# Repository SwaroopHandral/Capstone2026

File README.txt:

wsg chat
first commit type shit

new

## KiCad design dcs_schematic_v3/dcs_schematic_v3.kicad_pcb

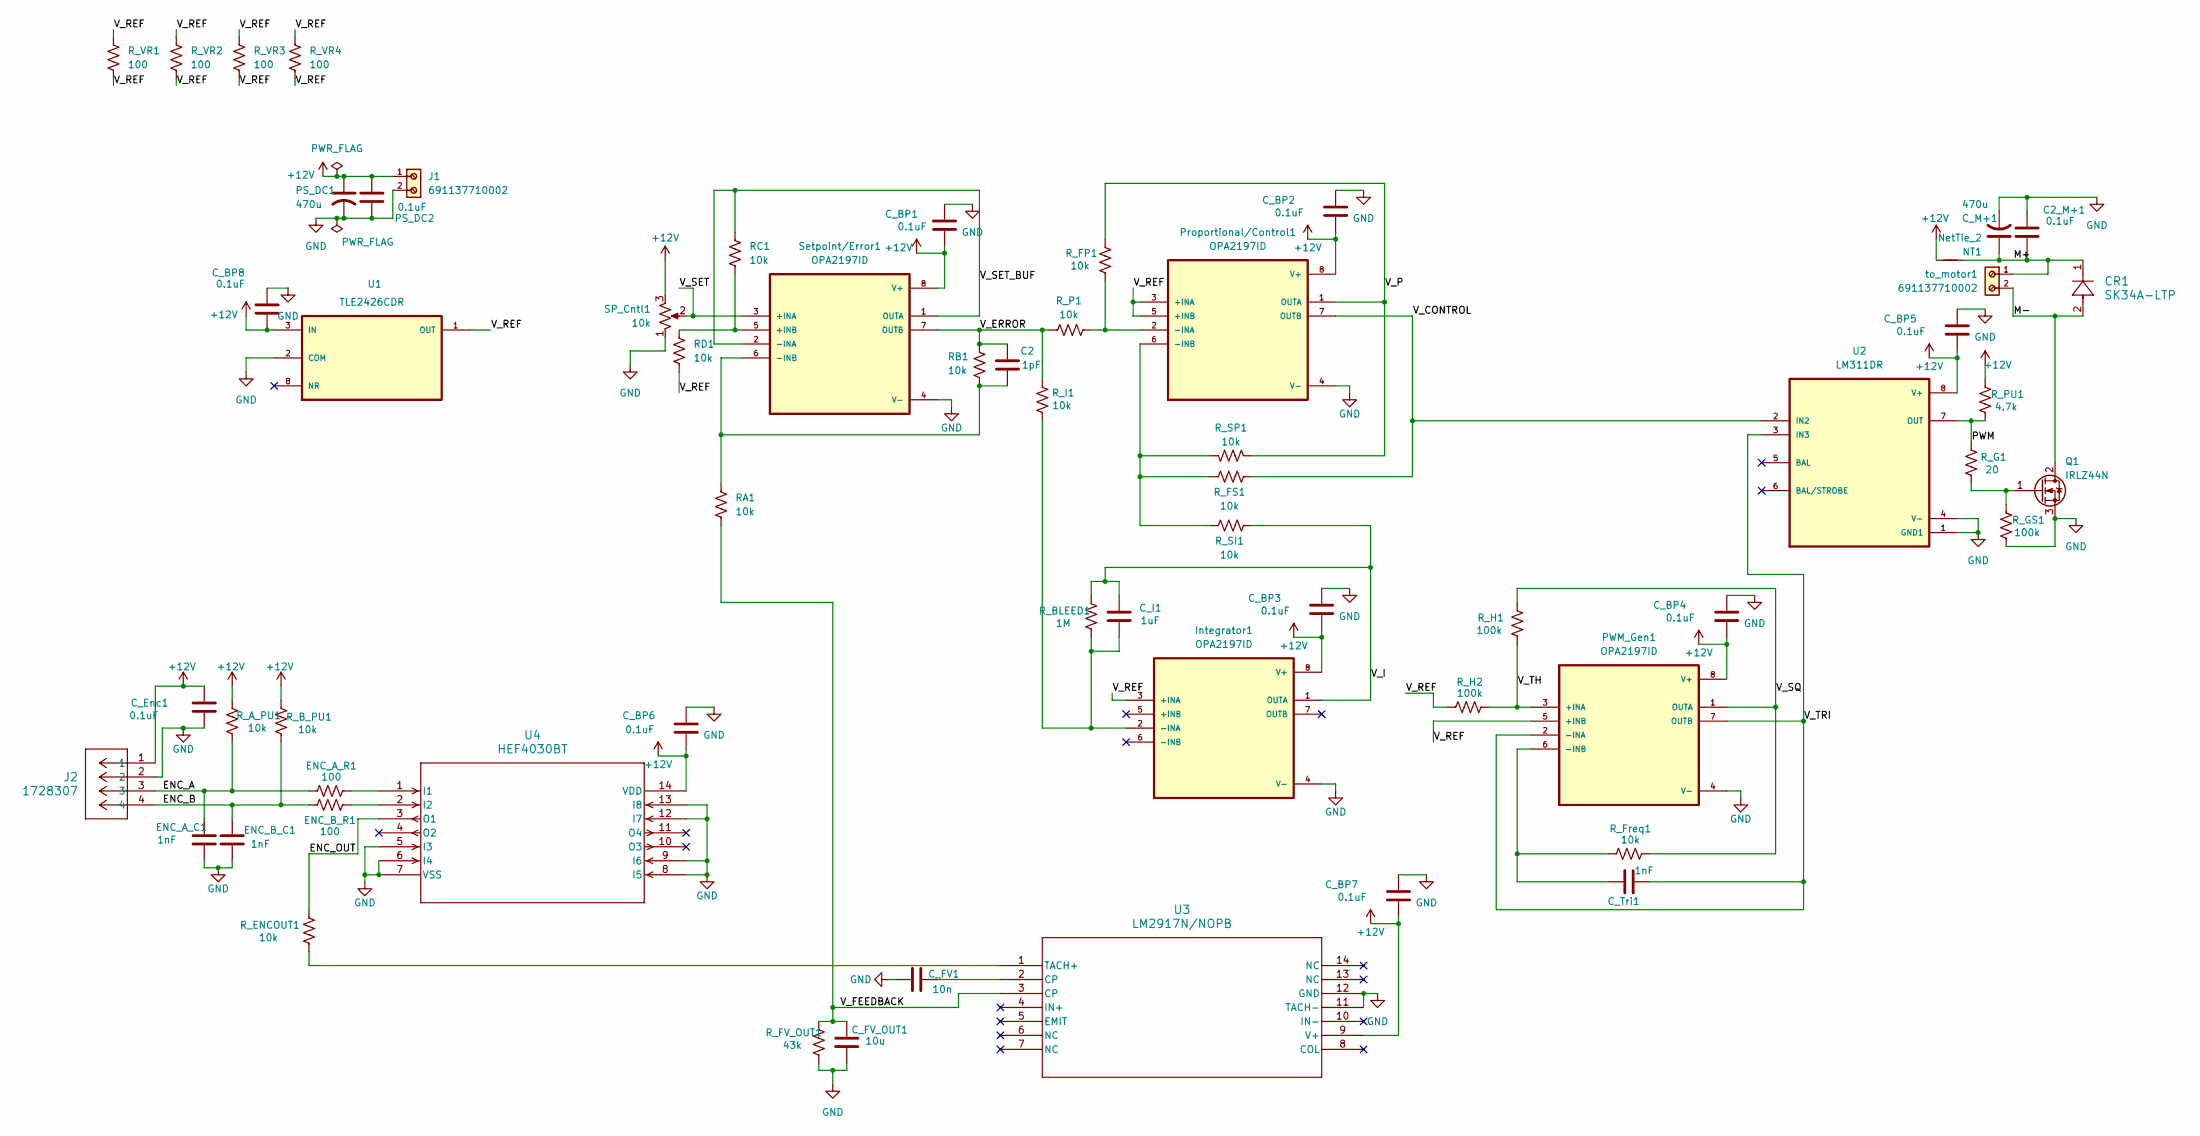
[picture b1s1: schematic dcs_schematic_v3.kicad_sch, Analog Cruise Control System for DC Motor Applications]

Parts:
C2: 1pF; C_0603_1608Metric_Pad1.08x0.95mm_HandSolder
C2_M+1: 0.1uF; C_0603_1608Metric_Pad1.08x0.95mm_HandSolder
CR1: SK34A-LTP; SK32A-LTP_Diode
C_BP1, C_BP2, C_BP3, C_BP4, C_BP5, C_BP6, C_BP7, C_BP8: 0.1uF; C_0603_1608Metric_Pad1.08x0.95mm_HandSolder
C_Enc1: 0.1uF; C_0603_1608Metric_Pad1.08x0.95mm_HandSolder
C_FV1: 10n; C_0603_1608Metric_Pad1.08x0.95mm_HandSolder
C_FV_OUT1: 10u; C_0603_1608Metric_Pad1.08x0.95mm_HandSolder
C_I1: 1uF; C_0603_1608Metric_Pad1.08x0.95mm_HandSolder
C_M+1: 470u; CP_Radial_D10.0mm_P5.00mm
C_Tri1: 1nF; C_0603_1608Metric_Pad1.08x0.95mm_HandSolder
ENC_A_C1: 1nF; C_0603_1608Metric_Pad1.08x0.95mm_HandSolder
ENC_A_R1: 100; R_0603_1608Metric_Pad0.98x0.95mm_HandSolder
ENC_B_C1: 1nF; C_0603_1608Metric_Pad1.08x0.95mm_HandSolder
ENC_B_R1: 100; R_0603_1608Metric_Pad0.98x0.95mm_HandSolder
Integrator1: OPA2197ID
J1: 691137710002; TerminalBlock
J2: 1728307; Term_1728307_PXC
NT1: NetTie_2; NetTie-2_SMD_Pad2.0mm
PS_DC1: 470u; CP_Radial_D10.0mm_P5.00mm
PS_DC2: 0.1uF; C_0603_1608Metric_Pad1.08x0.95mm_HandSolder
PWM_Gen1: OPA2197ID
Proportional/Control1: OPA2197ID
Q1: IRLZ44N; TO-220-3_Vertical
RA1: 10k; R_0603_1608Metric_Pad0.98x0.95mm_HandSolder
RB1: 10k; R_0603_1608Metric_Pad0.98x0.95mm_HandSolder
RC1: 10k; R_0603_1608Metric_Pad0.98x0.95mm_HandSolder
RD1: 10k; R_0603_1608Metric_Pad0.98x0.95mm_HandSolder
R_A_PU1: 10k; R_0603_1608Metric_Pad0.98x0.95mm_HandSolder
R_BLEED1: 1M; R_0603_1608Metric_Pad0.98x0.95mm_HandSolder
R_B_PU1: 10k; R_0603_1608Metric_Pad0.98x0.95mm_HandSolder
R_ENCOUT1: 10k; R_0603_1608Metric_Pad0.98x0.95mm_HandSolder
R_FP1: 10k; R_0603_1608Metric_Pad0.98x0.95mm_HandSolder
R_FS1: 10k; R_0603_1608Metric_Pad0.98x0.95mm_HandSolder
R_FV_OUT1: 43k; R_0603_1608Metric_Pad0.98x0.95mm_HandSolder
R_Freq1: 10k; R_0603_1608Metric_Pad0.98x0.95mm_HandSolder
R_G1: 20; R_0603_1608Metric_Pad0.98x0.95mm_HandSolder
R_GS1: 100k; R_0603_1608Metric_Pad0.98x0.95mm_HandSolder
R_H1, R_H2: 100k; R_0603_1608Metric_Pad0.98x0.95mm_HandSolder
R_I1: 10k; R_0603_1608Metric_Pad0.98x0.95mm_HandSolder
R_P1: 10k; R_0603_1608Metric_Pad0.98x0.95mm_HandSolder
R_PU1: 4.7k; R_0603_1608Metric_Pad0.98x0.95mm_HandSolder
R_SI1: 10k; R_0603_1608Metric_Pad0.98x0.95mm_HandSolder
R_SP1: 10k; R_0603_1608Metric_Pad0.98x0.95mm_HandSolder
R_VR1, R_VR2, R_VR3, R_VR4: 100; R_0603_1608Metric_Pad0.98x0.95mm_HandSolder
SP_Cntl1: 10k; Potentiometer_Bourns_PTV09A-2_Single_Horizontal
Setpoint/Error1: OPA2197ID
U1: TLE2426CDR; VREF_TLE2426CDR
U2: LM311DR
U3: LM2917N/NOPB; LM2917M
U4: HEF4030BT; XOR4030B
to_motor1: 691137710002; TerminalBlock

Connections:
+12V: C_BP1.2, C_BP2.2, C_BP3.2, C_BP4.2, C_BP5.2, C_BP6.2, C_BP7.2, C_BP8.2, C_Enc1.1, Integrator1.8 (V+), J1.1, J2.1, NT1.2, PS_DC1.1, PS_DC2.2, PWM_Gen1.8 (V+), Proportional/Control1.8 (V+), R_A_PU1.2, R_B_PU1.2, R_PU1.2, SP_Cntl1.3, Setpoint/Error1.8 (V+), U1.3 (IN), U2.8 (V+), U3.9 (V+), U4.14 (VDD); also elsewhere on the board
/ENC_A: ENC_A_C1.1, ENC_A_R1.2, J2.3, R_A_PU1.1
/ENC_B: ENC_B_C1.1, ENC_B_R1.2, J2.4, R_B_PU1.1
/ENC_OUT: R_ENCOUT1.2, U4.3 (O1); also elsewhere on the board
/M+: C2_M+1.2, CR1.1, C_M+1.1, NT1.1, to_motor1.1
/M-: CR1.2, Q1.2 (D), to_motor1.2
/PWM: R_G1.2, R_PU1.1, U2.7 (OUT)
/V_CONTROL: Proportional/Control1.7 (OUTB), R_FS1.2, U2.2 (IN2); also elsewhere on the board
/V_ERROR: C2.1, RB1.1, R_I1.2, R_P1.1, Setpoint/Error1.7 (OUTB)
/V_FEEDBACK: C_FV_OUT1.1, RA1.1, R_FV_OUT1.2, U3.3 (CP)
/V_I: C_I1.1, Integrator1.1 (OUTA), R_BLEED1.2, R_SI1.2; also elsewhere on the board
/V_P: Proportional/Control1.1 (OUTA), R_FP1.2, R_SP1.1; also elsewhere on the board
/V_REF: Integrator1.3 (+INA), PWM_Gen1.5 (+INB), Proportional/Control1.3 (+INA), Proportional/Control1.5 (+INB), RD1.1, R_H2.2, R_VR1.1, R_VR1.2, R_VR2.1, R_VR2.2, R_VR3.1, R_VR3.2, R_VR4.1, R_VR4.2, U1.1 (OUT); also elsewhere on the board
/V_SET: SP_Cntl1.2, Setpoint/Error1.3 (+INA)
/V_SET_BUF: RC1.1, Setpoint/Error1.1 (OUTA), Setpoint/Error1.2 (-INA)
/V_SQ: PWM_Gen1.1 (OUTA), R_Freq1.1, R_H1.2
/V_TH: PWM_Gen1.3 (+INA), R_H1.1, R_H2.1
/V_TRI: C_Tri1.2, PWM_Gen1.2 (-INA), PWM_Gen1.7 (OUTB), U2.3 (IN3)
GND: C2_M+1.1, C_BP1.1, C_BP2.1, C_BP3.1, C_BP4.1, C_BP5.1, C_BP6.1, C_BP7.1, C_BP8.1, C_Enc1.2, C_FV1.2, C_FV_OUT1.2, C_M+1.2, ENC_A_C1.2, ENC_B_C1.2, Integrator1.4 (V-), J1.2, J2.2, PS_DC1.2, PS_DC2.1, PWM_Gen1.4 (V-), Proportional/Control1.4 (V-), Q1.3 (S), R_FV_OUT1.1, R_GS1.1, SP_Cntl1.1, Setpoint/Error1.4 (V-), U1.2 (COM), U2.1 (GND1), U2.4 (V-), U3.11 (TACH-), U3.12 (GND), U4.5 (I3), U4.6 (I4), U4.7 (VSS), U4.8 (I5), U4.9 (I6), U4.12 (I7), U4.13 (I8); also elsewhere on the board
unnamed: C_FV1.1, U3.2 (CP)
unnamed 20: C_I1.2, Integrator1.2 (-INA), R_BLEED1.1, R_I1.1; also elsewhere on the board
unnamed: C_Tri1.1, PWM_Gen1.6 (-INB), R_Freq1.2
unnamed 22: Proportional/Control1.2 (-INA), R_FP1.1, R_P1.2; also elsewhere on the board
unnamed 23: Proportional/Control1.6 (-INB), R_FS1.1, R_SI1.1, R_SP1.2; also elsewhere on the board
unnamed: Q1.1 (G), R_G1.1, R_GS1.2
unnamed: RC1.2, RD1.2, Setpoint/Error1.5 (+INB)
unnamed: C2.2, RA1.2, RB1.2, Setpoint/Error1.6 (-INB)
unnamed 27: R_ENCOUT1.1, U3.1 (TACH+); also elsewhere on the board
unnamed: ENC_A_R1.1, U4.1 (I1)
unnamed: ENC_B_R1.1, U4.2 (I2)

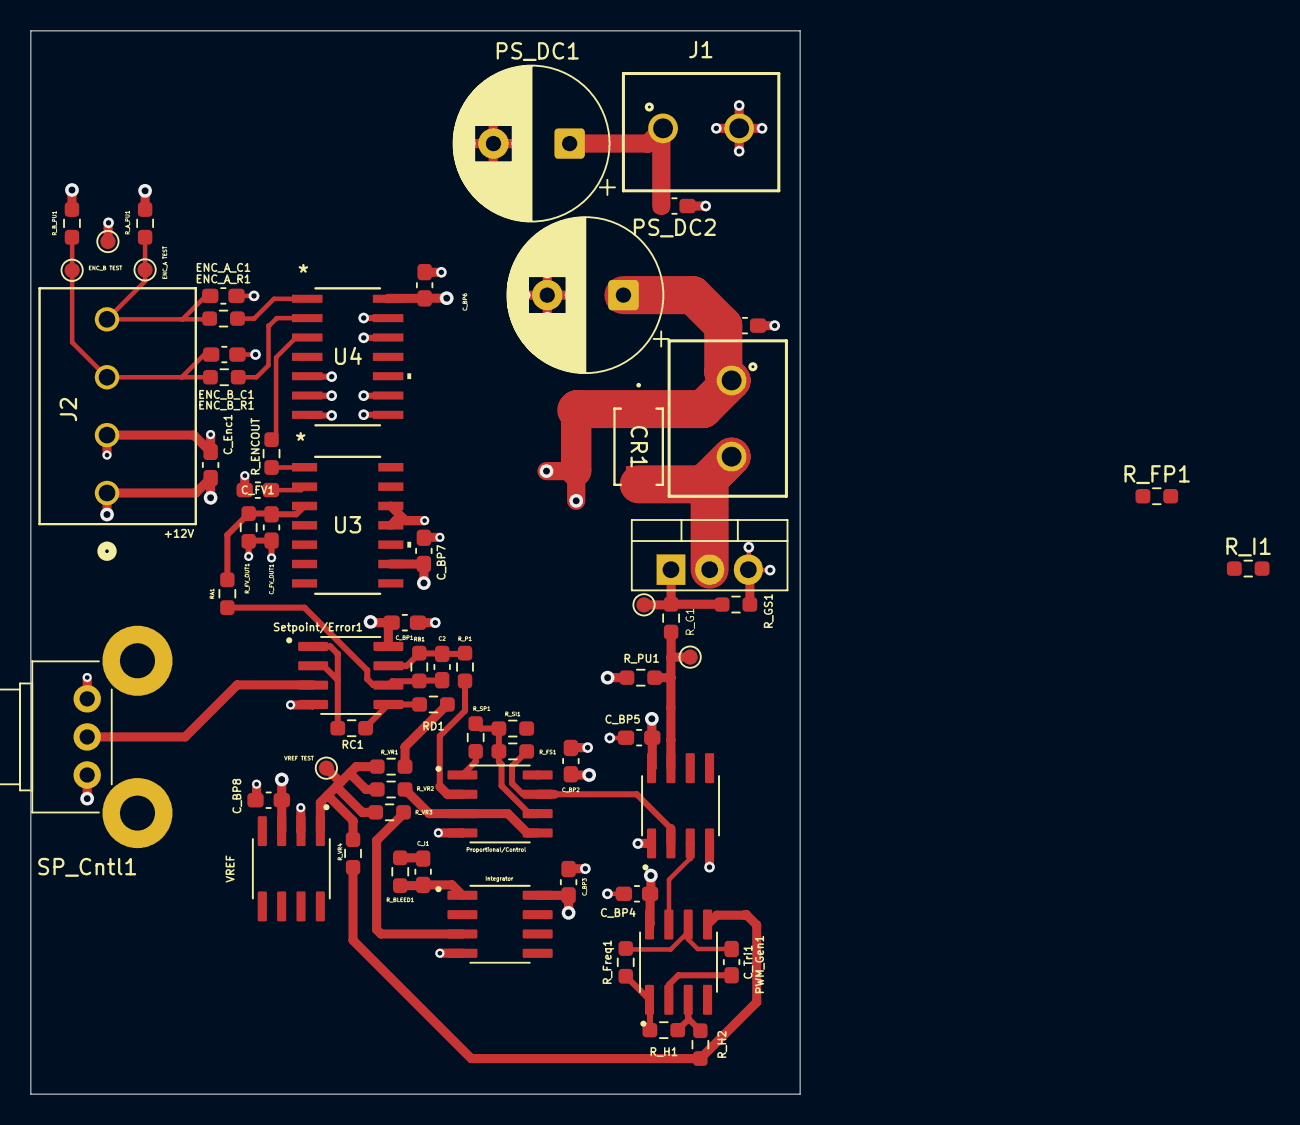
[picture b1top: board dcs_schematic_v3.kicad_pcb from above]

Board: 4 copper layers, 50.5 x 69.8 mm, 62 parts (0 on the bottom side), 30 nets.

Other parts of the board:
Integrator: OPA2197ID
Proportional/Control: OPA2197ID
R_ENCOUT: 10k; R_0603_1608Metric_Pad0.98x0.95mm_HandSolder
VREF: TLE2426CDR; VREF_TLE2426CDR

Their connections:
+12V: Integrator.8 (V+), Proportional/Control.8 (V+), VREF.3 (IN); also elsewhere on the board
/ENC_OUT: R_ENCOUT.2; also elsewhere on the board
/V_CONTROL: Proportional/Control.7 (OUTB); also elsewhere on the board
/V_I: Integrator.1 (OUTA); also elsewhere on the board
/V_P: Proportional/Control.1 (OUTA); also elsewhere on the board
/V_REF: Integrator.3 (+INA), Proportional/Control.3 (+INA), Proportional/Control.5 (+INB), VREF.1 (OUT); also elsewhere on the board
GND: Integrator.4 (V-), Proportional/Control.4 (V-), VREF.2 (COM); also elsewhere on the board
unnamed 20: Integrator.2 (-INA); also elsewhere on the board
unnamed 22: Proportional/Control.2 (-INA); also elsewhere on the board
unnamed 23: Proportional/Control.6 (-INB); also elsewhere on the board
unnamed 27: R_ENCOUT.1; also elsewhere on the board

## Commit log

2025-09-04 typeshit
2025-09-04 test commit
2025-09-04 added standards doc, datasheets, and reference pdfs
2025-09-09 added more datasheets, plus first version of schematic laid out in functional blocks. not yet wired
2025-09-09 changed ti084 to opa2197xD in schematic. swapped datasheets
2025-09-09 first version of wiring schematic 85% done
2025-09-11 finished v1 of wired circuit
2025-09-12 new cleaner schematic with correct parts and (hopefully) correct wiring. added datasheet for XOR gate. added kicad models for correct F/V converter.
2025-09-12 added power supplies for op-amps. will need to download correct models and update schematic
2025-09-12 Added Spice Model
2025-09-12 Add files via upload
    Spice Model files, .LIB file should be the one we're interested in
2025-09-18 annotated schematic for review
2025-09-18 updated kicad schematic, created personal microcap project
2025-09-18 added unofficial spice model for LM2917
2025-10-02 missing file
2025-10-06 removed pot from schematic
2025-10-07 added schematic v3 with real footprints. v4 will be simplified
2025-10-07 added kicad models and datasheets folder
2025-10-07 moved encoder datasheet to datasheet folder
2025-10-08 changed diode and updated datasheets/models accordingly. started PCB layout
2025-10-08 progress on PCB layout
2025-10-08 80-90% done with first PCB layout. Need to rework parts to fix traces
2025-10-08 changed diode again. updated datasheets, models, etc.
2025-10-09 schematic
2025-10-14 started v4 schematic, includes page with symbolic_schematic.kicad_sch
2025-10-17 schematic unfinished
2025-10-21 schemcatic
2025-10-24 added lm2917 model, changed .include file paths
2025-10-25 added derek's microcap schematic
    includes (possibly) working OPA2917 model
2025-10-26 updated schematic, library folder
    new schematic with working-ish motor logic. added MC12\Library to update my laptop with
2025-10-27 derek v2 of circuit
    might be kinda working
2025-10-27 schematic v3
2025-10-27 added sim screenshots, updated schematic
2025-10-28 bleh
2025-10-28 bruh
2025-10-28 microcap circuit v4
    small changes to circuit, added jpg for to replace easyeda logo on schematic
2025-10-28 Auto stash before merge of "main" and "origin/main"
2025-10-29 circuit v5
    also added some measurement screenshots, new motor datasheet, and new motor matlab script
2025-10-29 started matlab modeling
2025-10-30 functional diagram, pcb layout
    added kicad functional diagram schematic and started PCB design in EasyEDA
2025-10-31 working simulink model, added resources for DC motor modeling
2025-11-01 new matlab model
    working on new matlab model. trying to simulate torque feed-forward. added datasheet for current sense IC to experiment with feed forward
2025-11-09 pcb v1, bunch of other stuff
    finished and ordered pcb v1. added datasheets to new parts we need. other stuff I forget
2025-11-17 pcb v2
2025-11-17 screenshots
2025-11-23 pcb update and other stuff
2025-11-23 new pcb, datasheets, etc
2025-11-25 pcb schems
2025-11-25 new schem
2025-12-01 fixed pcb 1
2025-12-01 started new microcap schematic
2025-12-09 kicad schematic, datasheet, and figures
2025-12-11 adjusted figure size
2025-12-14 updated schematic
2025-12-18 updated schematic value, added block diagram.pdf
2026-03-10 final schematic update
2026-03-11 measurements
2026-03-12 adsf
2026-03-13 ghhkj
2026-03-13 matlab models and plots
2026-03-13 restored schematic
2026-04-12 final commit
    asdf
2026-04-12 actual last commit
    asd
2026-05-01 Auto stash before merge of "newest" and "origin/newest"
2026-05-01 asd
    dfas
